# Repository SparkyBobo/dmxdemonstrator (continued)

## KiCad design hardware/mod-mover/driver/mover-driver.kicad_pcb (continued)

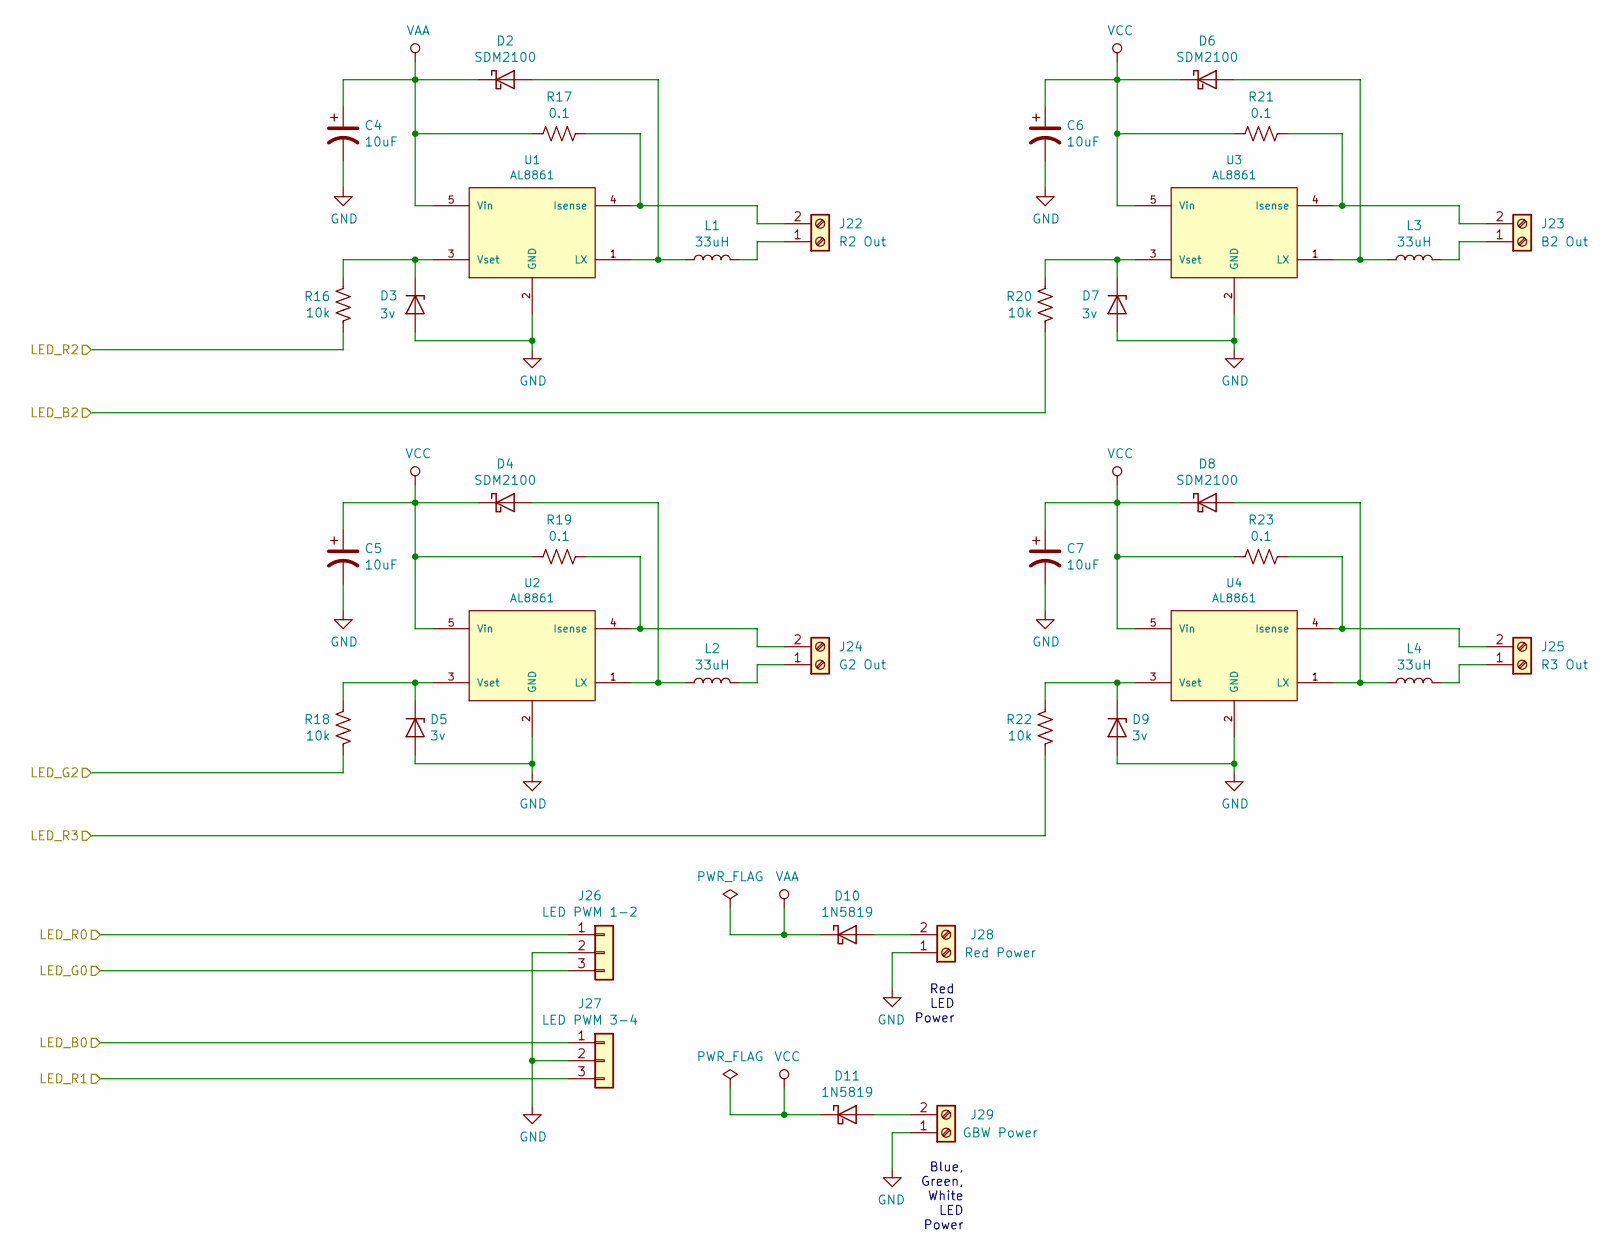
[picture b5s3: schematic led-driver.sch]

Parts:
C4, C5, C6, C7: 10uF; C_1206_3216Metric_Pad1.42x1.75mm_HandSolder; Digi-Key_PN P10425CT-ND
D2, D4, D6, D8: SDM2100; D_SOD-123F; Digi-Key_PN 1N5819-E3/54GITR-ND
D3, D5, D7, D9: 3v; D_SOD-123F
D10, D11: 1N5819; D_SOD-123F; Digi-Key_PN 1N5819-E3/54GITR-ND
J22: R2 Out; PhoenixContact_MCV_1,5_2-G-3.81_1x02_P3.81mm_Vertical
J23: B2 Out; PhoenixContact_MCV_1,5_2-G-3.81_1x02_P3.81mm_Vertical
J24: G2 Out; PhoenixContact_MCV_1,5_2-G-3.81_1x02_P3.81mm_Vertical
J25: R3 Out; PhoenixContact_MCV_1,5_2-G-3.81_1x02_P3.81mm_Vertical
J26: LED PWM 1-2; PinHeader_1x03_P2.54mm_Vertical
J27: LED PWM 3-4; PinHeader_1x03_P2.54mm_Vertical
J28: Red Power; PhoenixContact_MCV_1,5_2-G-3.81_1x02_P3.81mm_Vertical; Digi-Key_PN 277-1106-ND
J29: GBW Power; PhoenixContact_MCV_1,5_2-G-3.81_1x02_P3.81mm_Vertical; Digi-Key_PN 277-1106-ND
L1, L2, L3, L4: 33uH; L_6.3x6.3_H3
R16, R18, R20, R22: 10k; R_1206_3216Metric_Pad1.42x1.75mm_HandSolder
R17, R19, R21, R23: 0.1; R_1206_3216Metric_Pad1.42x1.75mm_HandSolder
U1, U2, U3, U4: AL8861; TSOT25

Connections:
/LED_B0: J27.1; also elsewhere on the board
/LED_B2: R20.1; also elsewhere on the board
/LED_G0: J26.3; also elsewhere on the board
/LED_G2: R18.1; also elsewhere on the board
/LED_R0: J26.1; also elsewhere on the board
/LED_R1: J27.3; also elsewhere on the board
/LED_R2: R16.1; also elsewhere on the board
/LED_R3: R22.1; also elsewhere on the board
GND: C4.2, C5.2, C6.2, C7.2, D3.2 (A), D5.2 (A), D7.2 (A), D9.2 (A), J26.2, J27.2, J28.1, J29.1, U1.2 (GND), U2.2 (GND), U3.2 (GND), U4.2 (GND); also elsewhere on the board
unnamed: D2.2 (A), L1.1, U1.1 (LX)
unnamed: D3.1 (K), R16.2, U1.3 (Vset)
unnamed: D4.2 (A), L2.1, U2.1 (LX)
unnamed: D5.1 (K), R18.2, U2.3 (Vset)
unnamed: D6.2 (A), L3.1, U3.1 (LX)
unnamed: D7.1 (K), R20.2, U3.3 (Vset)
unnamed: D8.2 (A), L4.1, U4.1 (LX)
unnamed: D9.1 (K), R22.2, U4.3 (Vset)
unnamed: D10.2 (A), J28.2
unnamed: D11.2 (A), J29.2
unnamed: J22.1, L1.2
unnamed: J22.2, R17.1, U1.4 (Isense)
unnamed: J23.1, L3.2
unnamed: J23.2, R21.1, U3.4 (Isense)
unnamed: J24.1, L2.2
unnamed: J24.2, R19.1, U2.4 (Isense)
unnamed: J25.1, L4.2
unnamed: J25.2, R23.1, U4.4 (Isense)
VAA: C4.1, D2.1 (K), D10.1 (K), R17.2, U1.5 (Vin); also elsewhere on the board
VCC: C5.1, C6.1, C7.1, D4.1 (K), D6.1 (K), D8.1 (K), D11.1 (K), R19.2, R21.2, R23.2, U2.5 (Vin), U3.5 (Vin), U4.5 (Vin); also elsewhere on the board

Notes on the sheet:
Blue, Green, White LED Power
Red LED Power

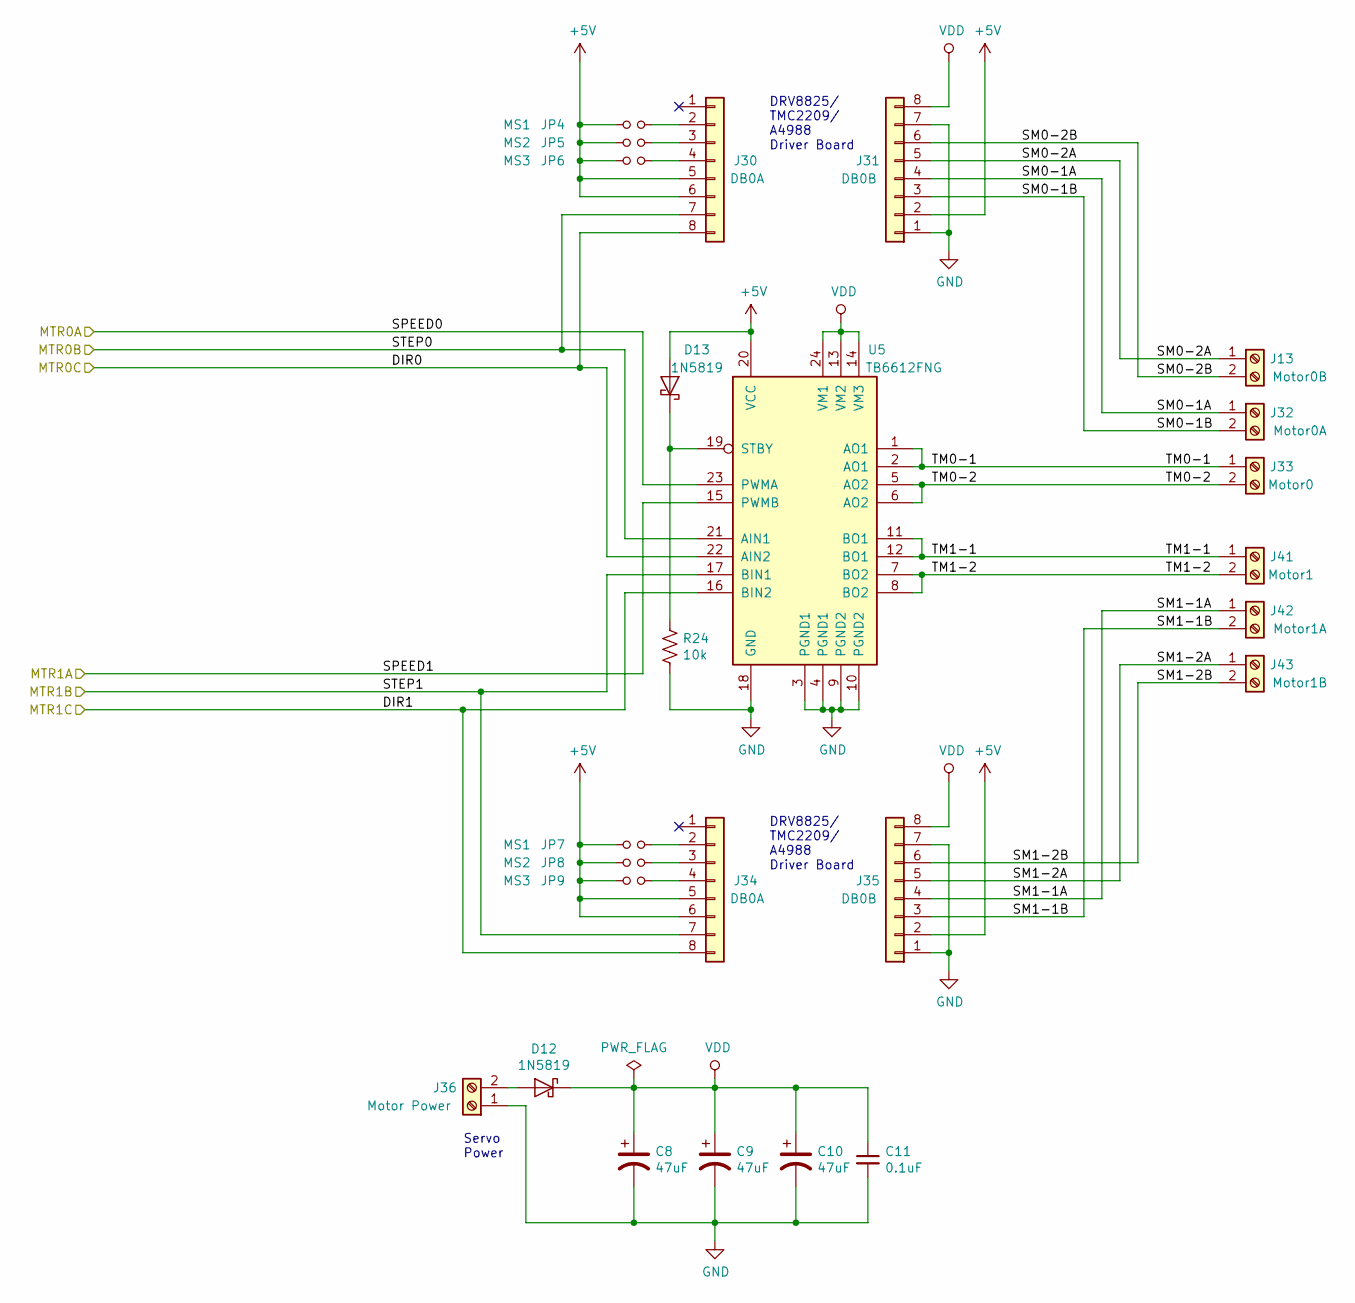
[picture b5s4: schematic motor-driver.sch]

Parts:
C8, C9, C10: 47uF; C_1206_3216Metric_Pad1.42x1.75mm_HandSolder; Digi-Key_PN P10425CT-ND
C11: 0.1uF; C_1206_3216Metric_Pad1.42x1.75mm_HandSolder
D12, D13: 1N5819; D_SOD-123F; Digi-Key_PN 1N5819-E3/54GITR-ND
J13: Motor0B; PhoenixContact_MCV_1,5_2-G-3.81_1x02_P3.81mm_Vertical
J30, J34: DB0A; PinHeader_1x08_P2.54mm_Vertical
J31, J35: DB0B; PinHeader_1x08_P2.54mm_Vertical
J32: Motor0A; PhoenixContact_MCV_1,5_2-G-3.81_1x02_P3.81mm_Vertical
J33: Motor0; PhoenixContact_MCV_1,5_2-G-3.81_1x02_P3.81mm_Vertical
J36: Motor Power; PhoenixContact_MCV_1,5_2-G-3.81_1x02_P3.81mm_Vertical
J41: Motor1; PhoenixContact_MCV_1,5_2-G-3.81_1x02_P3.81mm_Vertical
J42: Motor1A; PhoenixContact_MCV_1,5_2-G-3.81_1x02_P3.81mm_Vertical
J43: Motor1B; PhoenixContact_MCV_1,5_2-G-3.81_1x02_P3.81mm_Vertical
JP4, JP7: MS1; PinHeader_1x02_P2.54mm_Vertical
JP5, JP8: MS2; PinHeader_1x02_P2.54mm_Vertical
JP6, JP9: MS3; PinHeader_1x02_P2.54mm_Vertical
R24: 10k; R_1206_3216Metric_Pad1.42x1.75mm_HandSolder
U5: TB6612FNG; SSOP-24_5.3x8.2mm_P0.65mm

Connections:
+5V: D13.2 (A), J30.5, J30.6, J31.2, J34.5, J34.6, J35.2, JP4.1, JP5.1, JP6.1, JP7.1, JP8.1, JP9.1, U5.20 (VCC); also elsewhere on the board
/MTR0A: U5.23 (PWMA); also elsewhere on the board
/MTR0B: J30.7, U5.21 (AIN1); also elsewhere on the board
/MTR0C: J30.8, U5.22 (AIN2); also elsewhere on the board
/MTR1A: U5.15 (PWMB); also elsewhere on the board
/MTR1B: J34.7, U5.17 (BIN1); also elsewhere on the board
/MTR1C: J34.8, U5.16 (BIN2); also elsewhere on the board
/motor-driver/SM0-1A: J31.4, J32.1
/motor-driver/SM0-1B: J31.3, J32.2
/motor-driver/SM0-2A: J13.1, J31.5
/motor-driver/SM0-2B: J13.2, J31.6
/motor-driver/SM1-1A: J35.4, J42.1
/motor-driver/SM1-1B: J35.3, J42.2
/motor-driver/SM1-2A: J35.5, J43.1
/motor-driver/SM1-2B: J35.6, J43.2
/motor-driver/TM0-1: J33.1, U5.1 (AO1), U5.2 (AO1)
/motor-driver/TM0-2: J33.2, U5.5 (AO2), U5.6 (AO2)
/motor-driver/TM1-1: J41.1, U5.11 (BO1), U5.12 (BO1)
/motor-driver/TM1-2: J41.2, U5.7 (BO2), U5.8 (BO2)
GND: C8.2, C9.2, C10.2, C11.2, J31.1, J31.7, J35.1, J35.7, J36.1, R24.2, U5.3 (PGND1), U5.4 (PGND1), U5.9 (PGND2), U5.10 (PGND2), U5.18 (GND); also elsewhere on the board
unnamed: D12.2 (A), J36.2
unnamed: D13.1 (K), R24.1, U5.19 (STBY)
unnamed: J30.2, JP4.2
unnamed: J30.3, JP5.2
unnamed: J30.4, JP6.2
unnamed: J34.2, JP7.2
unnamed: J34.3, JP8.2
unnamed: J34.4, JP9.2
VDD: C8.1, C9.1, C10.1, C11.1, D12.1 (K), J31.8, J35.8, U5.13 (VM2), U5.14 (VM3), U5.24 (VM1); also elsewhere on the board

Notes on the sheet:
DRV8825/ TMC2209/ A4988 Driver Board
Servo Power

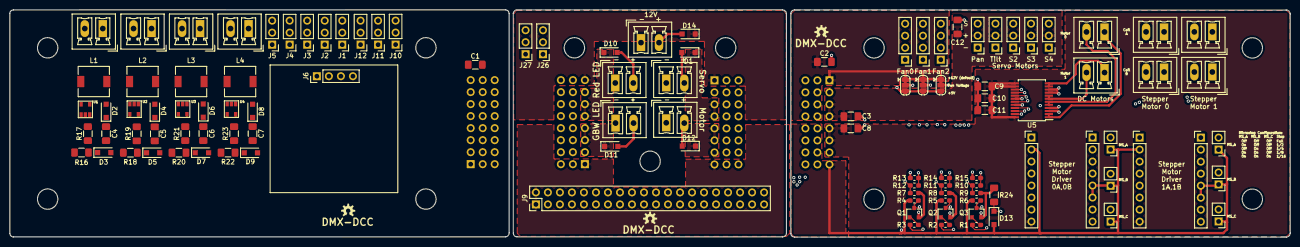
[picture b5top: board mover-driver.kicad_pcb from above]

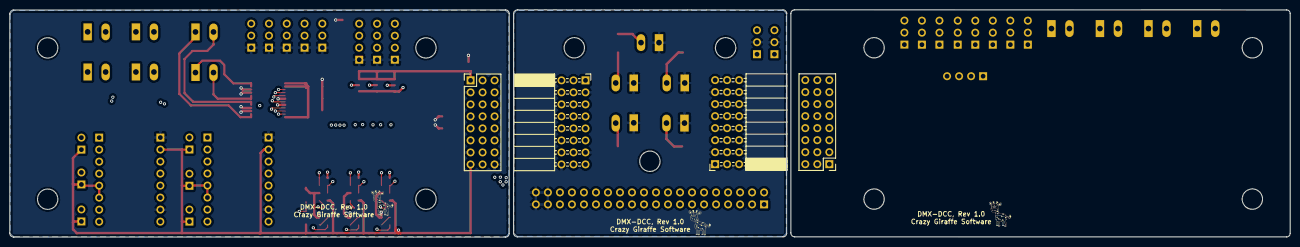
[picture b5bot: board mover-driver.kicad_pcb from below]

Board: 4 copper layers, 270.8 x 48.1 mm, 125 parts (4 on the bottom side), 92 nets.

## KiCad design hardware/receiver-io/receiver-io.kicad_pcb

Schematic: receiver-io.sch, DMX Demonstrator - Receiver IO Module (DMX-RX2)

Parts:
A1: Arduino_UNO_R3; ARDUINO_R3_NO_HOLES
J1, J2: IO EXTENSION; IDC-Header_2x07_P2.54mm_Horizontal

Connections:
+5V: A1.5, J1.1, J1.2, J2.1, J2.2
/A0: A1.9, J1.7, J2.7
/A1: A1.10, J1.5, J2.5
/DMX-DIR: A1.17, J1.10, J2.10
/DMX-RX: A1.15, J1.9, J2.9
/DMX-TX: A1.16, J1.11, J2.11
/SR-CLK: A1.19, J1.6, J2.6
/SR-OUT: A1.18, J1.4, J2.4
/~SR_CLR: A1.22, J1.8, J2.8
/~WR: A1.23, J1.3, J2.3
GND: A1.6, A1.7, A1.29, J1.13, J1.14, J2.13, J2.14

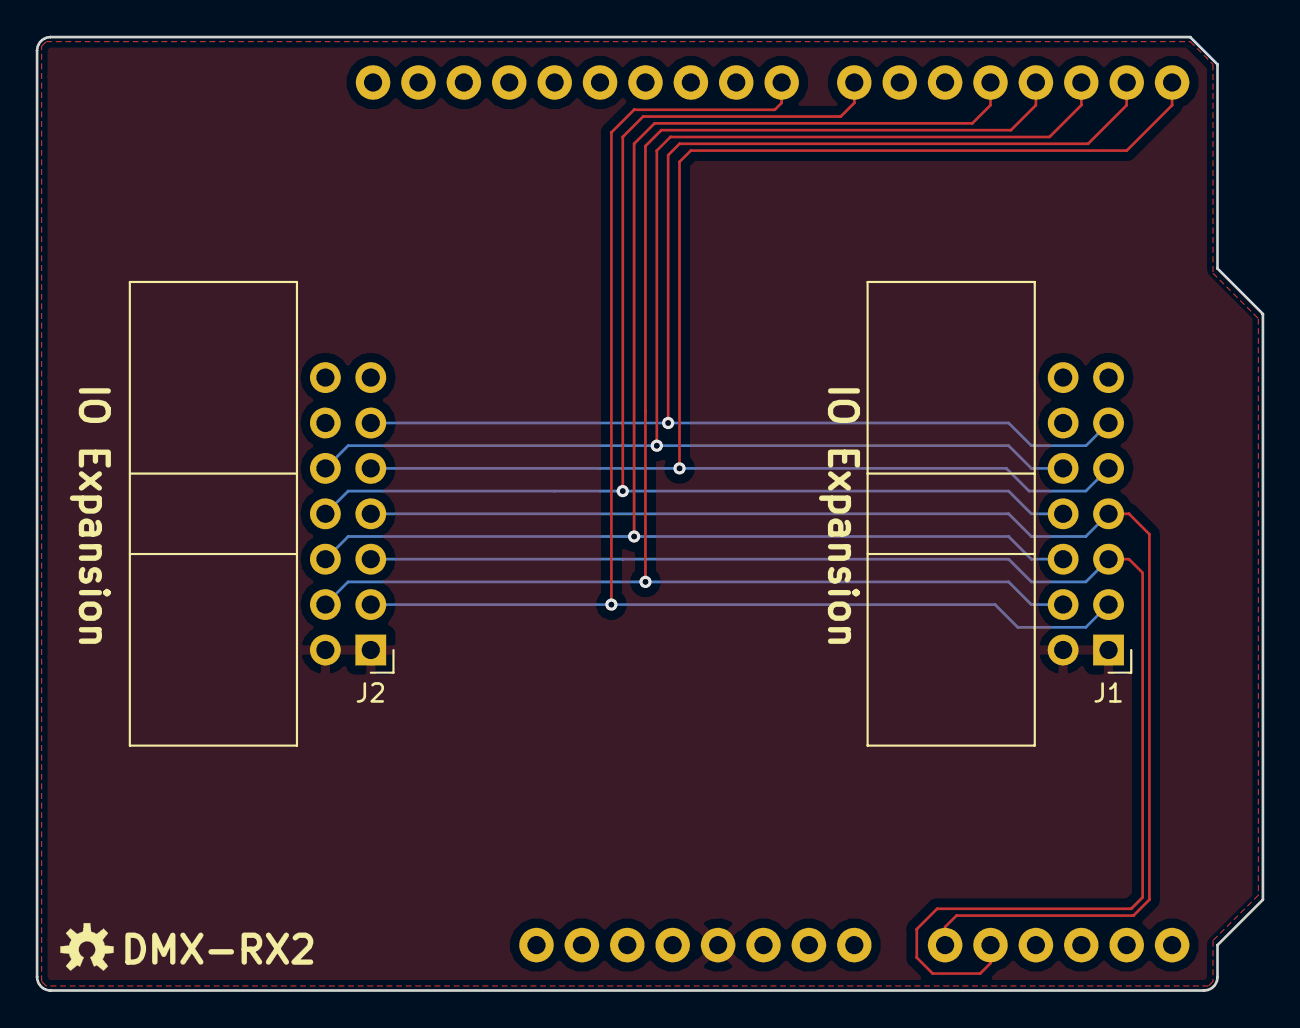
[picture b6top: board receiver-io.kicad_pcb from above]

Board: 2 copper layers, 68.6 x 53.3 mm, 3 parts (0 on the bottom side), 11 nets.

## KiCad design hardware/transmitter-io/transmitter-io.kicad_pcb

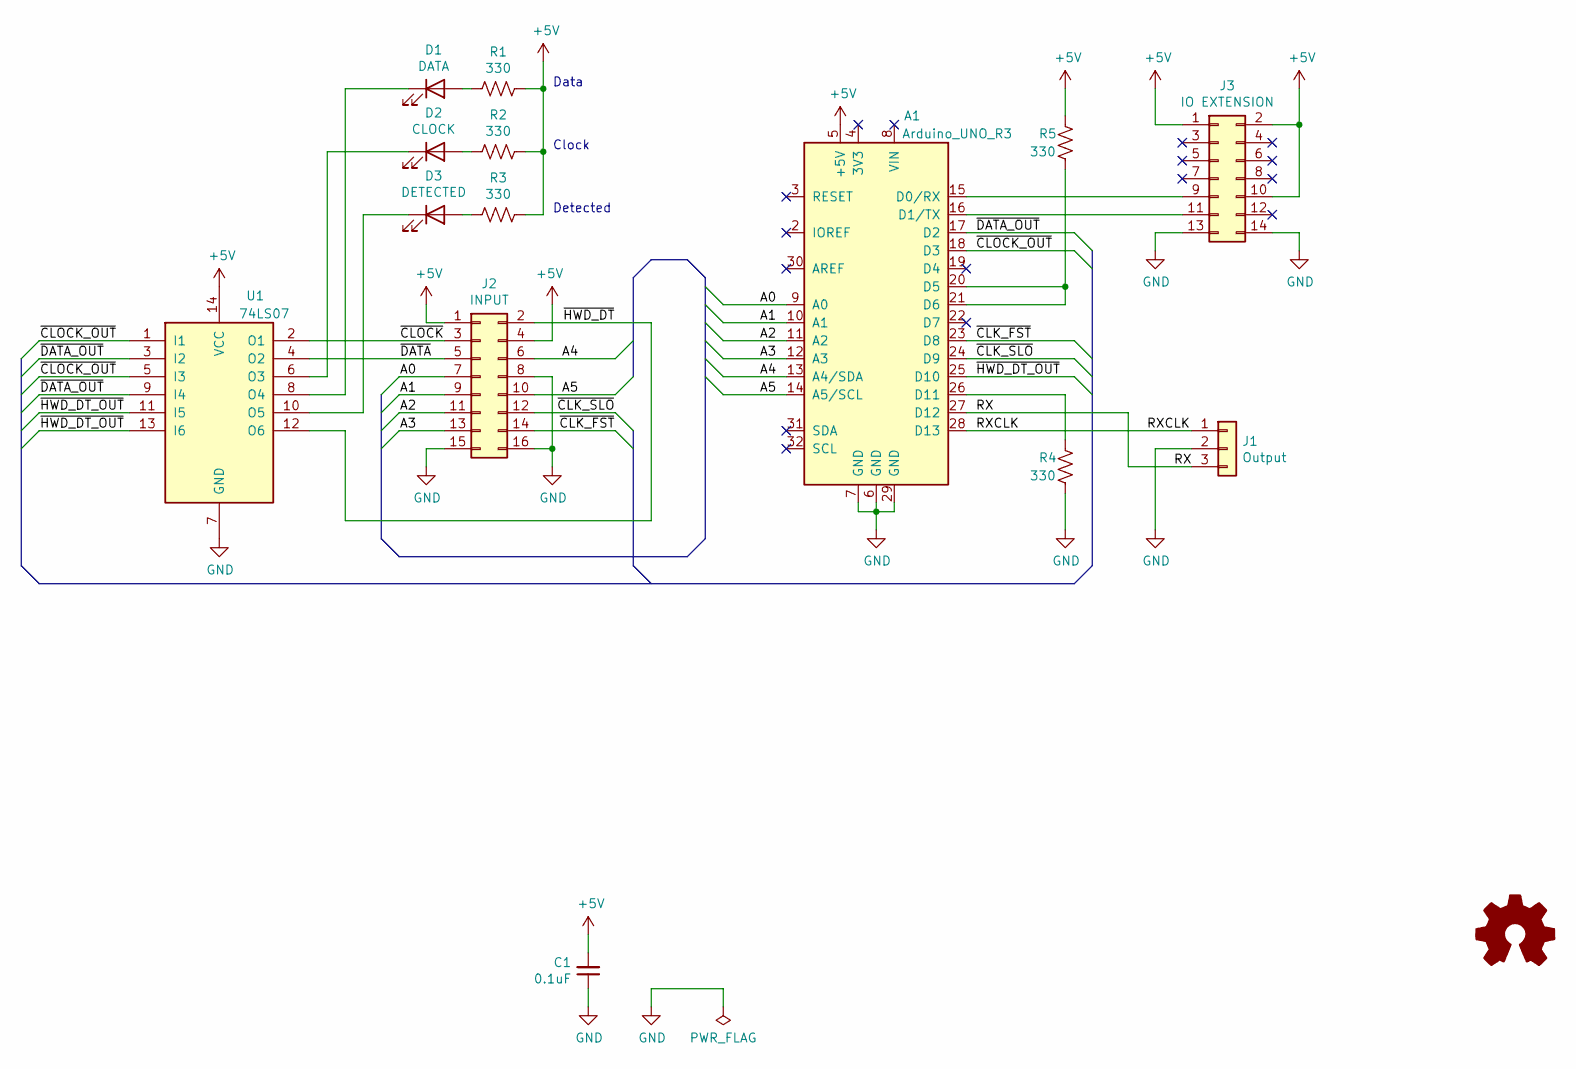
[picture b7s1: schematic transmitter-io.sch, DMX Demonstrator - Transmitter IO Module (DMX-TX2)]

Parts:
A1: Arduino_UNO_R3; ARDUINO_R3_NO_HOLES
C1: 0.1uF; C_Disc_D3.0mm_W1.6mm_P2.50mm
D1: DATA; LED_D5.0mm
D2: CLOCK; LED_D5.0mm
D3: DETECTED; LED_D5.0mm
J1: Output; PinHeader_1x03_P2.54mm_Horizontal
J2: INPUT; IDC-Header_2x08_P2.54mm_Vertical
J3: IO EXTENSION; IDC-Header_2x07_P2.54mm_Horizontal
R1, R2, R3, R4, R5: 330; R_Axial_DIN0207_L6.3mm_D2.5mm_P10.16mm_Horizontal
U1: 74LS07; DIP-14_W7.62mm

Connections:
+5V: A1.5 (+5V), C1.2, J2.1, J2.4, J3.1, J3.2, J3.10, R1.1, R2.1, R3.1, R5.1, U1.14 (VCC)
/A0: A1.9 (A0), J2.7
/A1: A1.10 (A1), J2.9
/A2: A1.11 (A2), J2.11
/A3: A1.12 (A3), J2.13
/A4: A1.13 (A4/SDA), J2.6
/A5: A1.14 (A5/SCL), J2.10
/RX: A1.27 (D12), J1.3
/RXCLK: A1.28 (D13), J1.1
/~CLK_FST: A1.23 (D8), J2.14
/~CLK_SLO: A1.24 (D9), J2.12
/~CLOCK: J2.3, U1.2 (O1)
/~CLOCK_OUT: A1.18 (D3), U1.1 (I1), U1.5 (I3)
/~DATA: J2.5, U1.4 (O2)
/~DATA_OUT: A1.17 (D2), U1.3 (I2), U1.9 (I4)
/~HWD_DT: J2.2, U1.12 (O6)
/~HWD_DT_OUT: A1.25 (D10), U1.11 (I5), U1.13 (I6)
GND: A1.6 (GND), A1.7 (GND), A1.29 (GND), C1.1, J1.2, J2.8, J2.15, J2.16, J3.13, J3.14, R4.2, U1.7 (GND)
unnamed: A1.15 (D0/RX), J3.9
unnamed: A1.16 (D1/TX), J3.11
unnamed: A1.20 (D5), A1.21 (D6), R5.2
unnamed: A1.26 (D11), R4.1
unnamed: D1.1 (K), U1.8 (O4)
unnamed: D1.2 (A), R1.2
unnamed: D2.1 (K), U1.6 (O3)
unnamed: D2.2 (A), R2.2
unnamed: D3.1 (K), U1.10 (O5)
unnamed: D3.2 (A), R3.2

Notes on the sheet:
Clock
Data
Detected

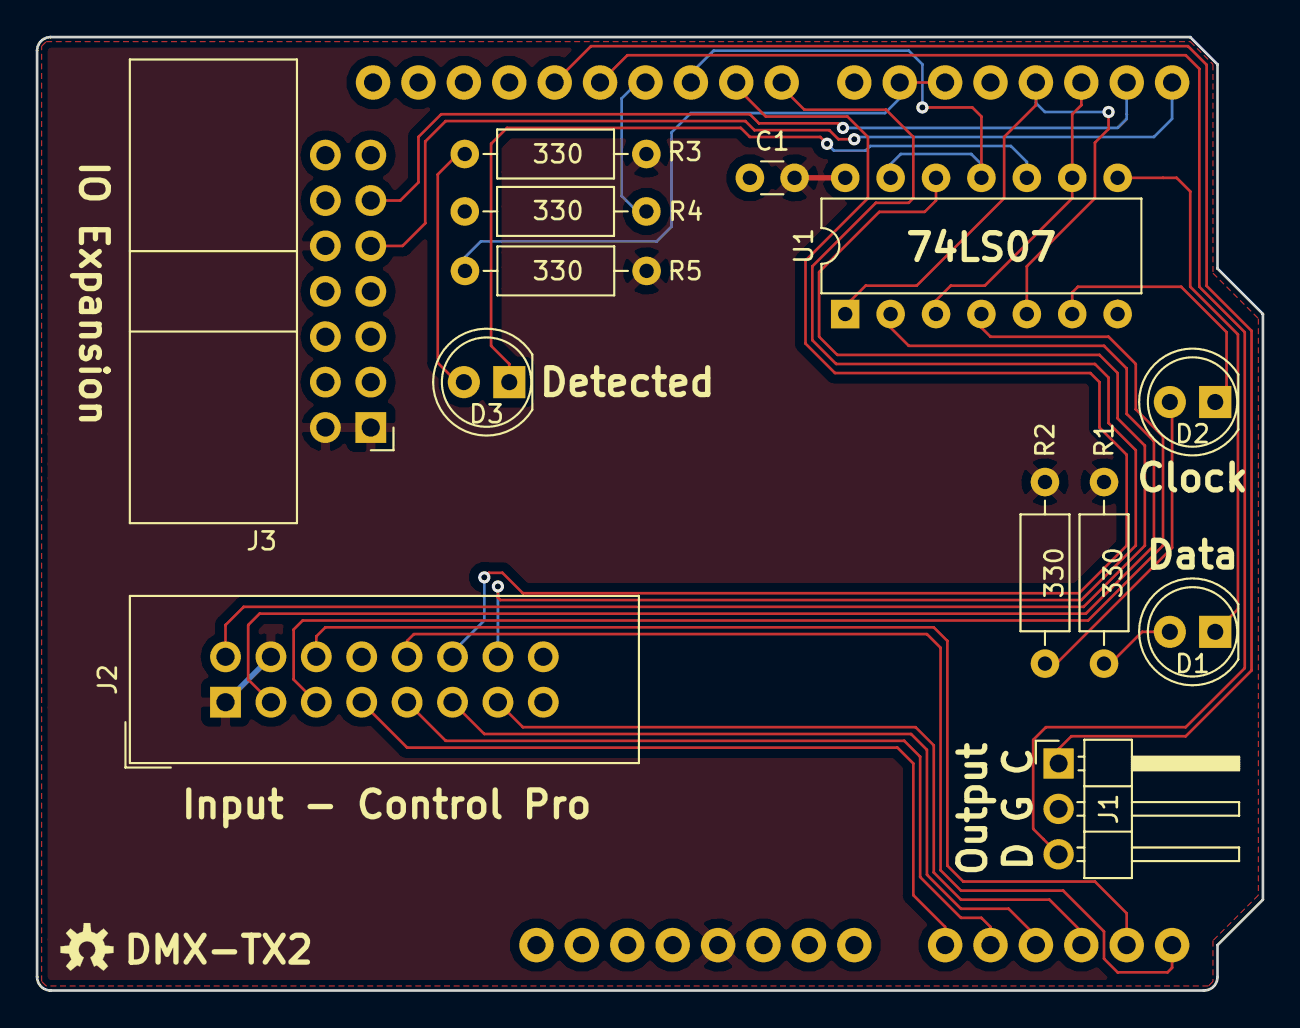
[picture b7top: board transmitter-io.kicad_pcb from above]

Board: 2 copper layers, 68.6 x 53.3 mm, 14 parts (0 on the bottom side), 28 nets.

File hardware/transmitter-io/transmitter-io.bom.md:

# Bill Of Materials (BOM)

## Schematic

**Filename:** E:\OpenSource\dmxdemonstrator\hardware\transmitter-io\transmitter-io.sch

**Date Modified:** 3/31/2024 9:17:45 PM

**Kicad Version:** Eeschema (5.1.12)-1

**Component Count:** 14

## Components

Item#|Quantity|Reference|Description|Manufacturer|Part Number|Datasheet|Notes
-----|--------|---------|-----------|------------|-----------|---------|-----
1|1|PCB|Transmitter IO PCB|OHSPark|DMX-TX2, Rev 1.3||[Order](https://oshpark.com/shared_projects/mKdzHGgN)|
2|1|A1|Arduino UNO/Leonardo|||[Data Sheet](https://www.arduino.cc/en/Main/arduinoBoardUno)|
3|1|A1|Arduino R3 Headers|||[Data Sheet](https://www.arduino.cc/en/Main/arduinoBoardUno)|
4|1|C1|0.1uF||||
5|1|D1|Green LED, 5mm||||
6|1|D2|Red LED, 5mm||||
7|1|D3|Red LED, 5mm||||
8|1|J1|3-pin right-angle header||||
9|1|J2|2x8 shrouded header|Wurth Elektronik|61201621621|[Data Sheet](https://www.we-online.com/catalog/datasheet/61201621621.pdf)|
10|1|J3|2x7 shrouded right-angle header|Wurth Elektronik|61201421721|[Data Sheet](https://www.we-online.com/catalog/datasheet/61201421721.pdf)|
11|5|R1, R2, R3, R4, R5|330 ohm||||
12|1|U1|74LS07|Texas Instruments|SN74LS07N|[Data Sheet](https://www.ti.com/lit/gpn/sn74ls07)|
<!--BOMROW-->
